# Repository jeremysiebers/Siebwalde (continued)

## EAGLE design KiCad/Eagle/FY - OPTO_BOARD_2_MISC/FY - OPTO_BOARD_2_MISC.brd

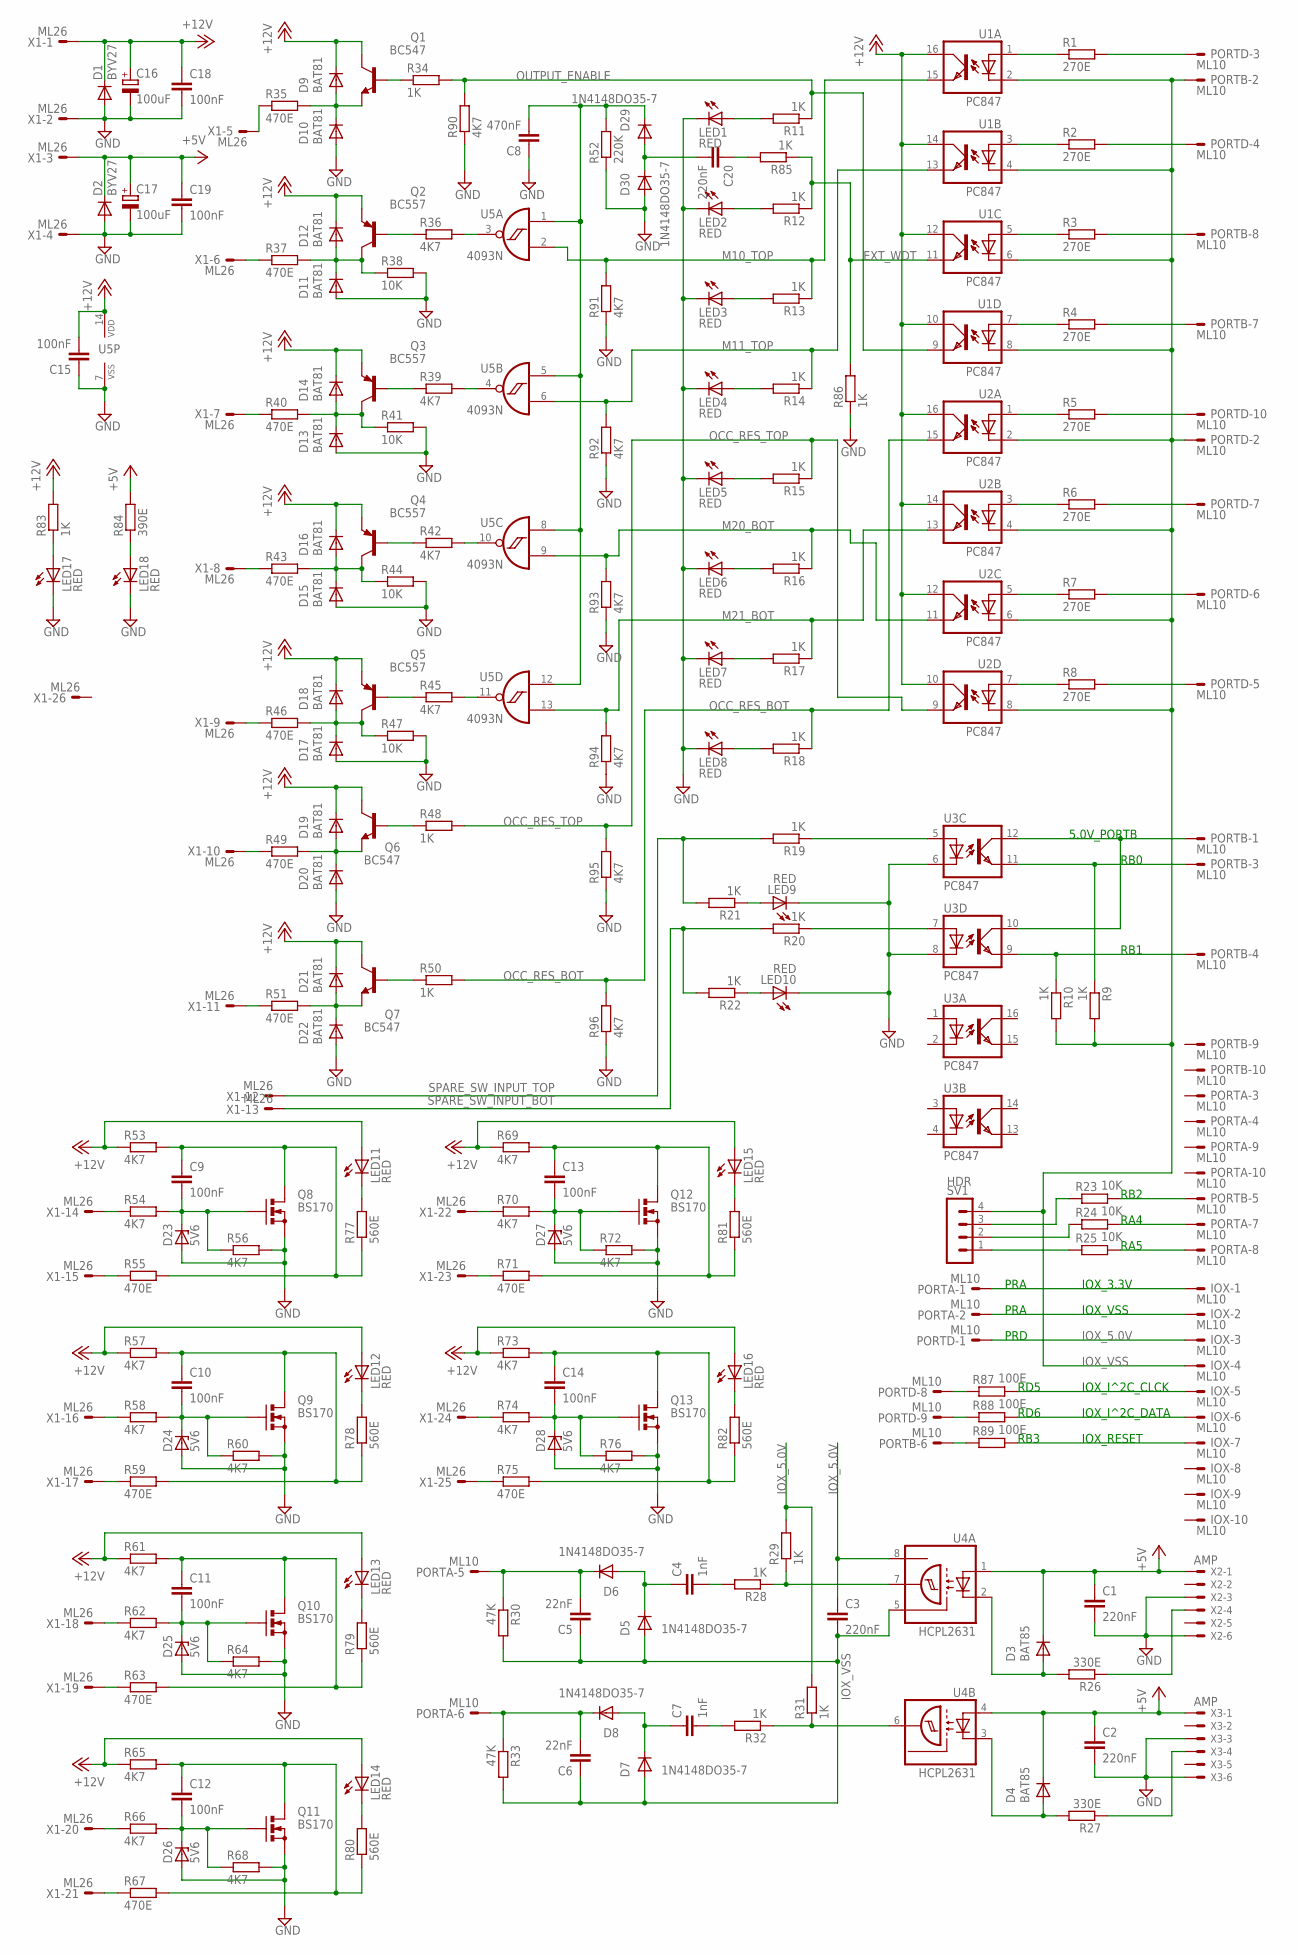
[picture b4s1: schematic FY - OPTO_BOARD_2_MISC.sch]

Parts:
C1, C2, C3, C20: 220nF; C050-025X075
C4, C7: 1nF; C050-025X075
C5, C6: 22nF; C050-025X075
C8: 470nF; C050-025X075
C9, C10, C11, C12, C13, C14, C15, C18, C19: 100nF; C050-025X075
C16, C17: 100uF; E5-8,5
D1, D2: BYV27; SOD57-10
D3, D4: BAT85; DO34-7
D5, D6, D7, D8, D29, D30: 1N4148DO35-7; DO35-7
D9, D10, D11, D12, D13, D14, D15, D16, D17, D18, D19, D20, D21, D22: BAT81; DO34-7
D23, D24, D25, D26, D27, D28: 5V6; DO34Z7
IOX: ML10
LED1, LED2, LED3, LED4, LED5, LED6, LED7, LED8, LED9, LED10, LED11, LED12, LED13, LED14, LED15, LED16, LED17, LED18: RED; LED3MM
PORTA: ML10
PORTB: ML10
PORTD: ML10
Q1, Q6, Q7: BC547; TO92
Q2, Q3, Q4, Q5: BC557; TO92
Q8, Q9, Q10, Q11, Q12, Q13: BS170; SOT54E
R1, R2, R3, R4, R5, R6, R7, R8: 270E; 0207/10
R9, R10, R11, R12, R13, R14, R15, R16, R17, R18, R19, R20, R21, R22, R28, R29, R31, R32, R34, R48, R50, R83, R85, R86: 1K; 0207/10
R23, R24, R25, R38, R41, R44, R47: 10K; 0207/10
R26, R27: 330E; 0207/10
R30, R33: 47K; 0207/10
R35, R37, R40, R43, R46, R49, R51, R55, R59, R63, R67, R71, R75: 470E; 0207/10
R36, R39, R42, R45, R53, R54, R56, R57, R58, R60, R61, R62, R64, R65, R66, R68, R69, R70, R72, R73, R74, R76, R90, R91, R92, R93, R94, R95, R96: 4K7; 0207/10
R52: 220K; 0207/10
R77, R78, R79, R80, R81, R82: 560E; 0207/10
R84: 390E; 0207/10
R87, R88, R89: 100E; 0207/10
SV1: HDR; MA04-1
U1, U2, U3: PC847; DIL16
U4: HCPL2631; DIL08
U5: 4093N; DIL14
X1: ML26
X2, X3: AMP; 22-23-2061

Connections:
+5V: C1.1, C2.1, C17.+, C19.1, D2.C, D3.C, D4.C, R84.2, U4.1 (A), U4.4 (A), X1.3, X2.1, X3.1
+12V: C15.2, C16.+, C18.1, D1.C, D9.C, D12.C, D14.C, D16.C, D18.C, D19.C, D21.C, LED11.A, LED12.A, LED13.A, LED14.A, LED15.A, LED16.A, Q1.3 (C), Q2.1 (E), Q3.1 (E), Q4.1 (E), Q5.1 (E), Q6.3 (C), Q7.3 (C), R53.1, R57.1, R61.1, R65.1, R69.1, R73.1, R83.2, U1.10 (COL), U1.12 (COL), U1.14 (COL), U1.16 (COL), U2.10 (COL), U2.12 (COL), U2.14 (COL), U2.16 (COL), U5.14 (VDD), X1.1
EXT_WDT: R12.1, R85.1, R86.2, U1.11 (EMIT)
GND: C1.2, C2.2, C8.1, C15.1, C16.-, C17.-, C18.2, C19.2, D1.A, D2.A, D10.A, D11.A, D13.A, D15.A, D17.A, D20.A, D22.A, D23.A, D24.A, D25.A, D26.A, D27.A, D28.A, D30.A, LED1.K (C), LED2.K (C), LED3.K (C), LED4.K (C), LED5.K (C), LED6.K (C), LED7.K (C), LED8.K (C), LED9.K (C), LED10.K (C), LED17.K (C), LED18.K (C), Q8.S, Q9.S, Q10.S, Q11.S, Q12.S, Q13.S, R38.2, R41.2, R44.2, R47.2, R52.1, R56.2, R60.2, R64.2, R68.2, R72.2, R76.2, R86.1, R90.1, R91.1, R92.1, R93.1, R94.1, R95.1, R96.1, U3.6 (C), U3.8 (C), U5.7 (VSS), X1.2, X1.4, X2.3, X2.6, X3.3, X3.6
IOX_5.0V: C3.1, IOX.3, PORTD.1, R29.2, R31.2, U4.8 (VCC)
IOX_VSS: C3.2, C5.1, C6.1, D5.A, D7.A, IOX.4, PORTB.2, PORTD.2, R9.2, R10.2, R30.2, R33.2, SV1.4, U1.2 (C), U1.4 (C), U1.6 (C), U1.8 (C), U2.2 (C), U2.4 (C), U2.6 (C), U2.8 (C), U4.5 (GND)
M10_TOP: R13.1, R91.2, U1.15 (EMIT), U5.2 (I1)
M11_TOP: R14.1, R92.2, U1.13 (EMIT), U5.6 (I1)
M20_BOT: R16.1, R93.2, U2.11 (EMIT), U5.9 (I1)
M21_BOT: R17.1, R94.2, U2.13 (EMIT), U5.13 (I1)
unnamed: R1.1, U1.1 (A)
unnamed: R2.1, U1.3 (A)
unnamed: R3.1, U1.5 (A)
unnamed: R4.1, U1.7 (A)
unnamed: LED1.A, R11.2
unnamed: LED2.A, R12.2
unnamed: LED3.A, R13.2
unnamed: LED4.A, R14.2
unnamed: Q2.2 (B), R36.1
unnamed: C10.1, Q9.D, R57.2, R59.2, R78.1
unnamed: C8.2, D29.C, R52.2, U5.1 (I0), U5.5 (I0), U5.8 (I0), U5.12 (I0)
unnamed: LED11.K (C), R77.2
unnamed: R23.1, SV1.3
unnamed: R5.1, U2.1 (A)
unnamed: R6.1, U2.3 (A)
unnamed: R7.1, U2.5 (A)
unnamed: R8.1, U2.7 (A)
unnamed: C9.2, D23.C, Q8.G, R54.2, R56.1
unnamed: R19.1, U3.5 (A)
unnamed: R20.1, U3.7 (A)
unnamed: LED12.K (C), R78.2
unnamed: LED5.A, R15.2
unnamed: LED6.A, R16.2
unnamed: LED7.A, R17.2
unnamed: LED8.A, R18.2
unnamed: PORTD.5, R8.2
unnamed: Q1.2 (B), R34.1
unnamed: PORTD.6, R7.2
unnamed: PORTD.7, R6.2
unnamed: PORTD.10, R5.2
unnamed: PORTD.4, R2.2
unnamed: PORTD.3, R1.2
unnamed: C10.2, D24.C, Q9.G, R58.2, R60.1
unnamed: LED9.A, R21.1
unnamed: LED10.A, R22.1
unnamed: PORTB.1, U3.10 (COL), U3.12 (COL)
unnamed: LED17.A, R83.1
unnamed: PORTB.8, R3.2
unnamed: PORTB.3, R9.1, U3.11 (EMIT)
unnamed: PORTB.4, R10.1, U3.9 (EMIT)
unnamed: PORTB.7, R4.2
unnamed: LED18.A, R84.1
unnamed: C4.2, R28.2
unnamed: R24.1, SV1.2
unnamed: R25.1, SV1.1
unnamed: PORTB.5, R23.2
unnamed: PORTA.7, R24.2
unnamed: PORTA.8, R25.2
unnamed: IOX.1, PORTA.1
unnamed: IOX.2, PORTA.2
unnamed: IOX.7, R89.2
unnamed: IOX.5, R87.2
unnamed: IOX.6, R88.2
unnamed: D9.A, D10.C, Q1.1 (E), R35.2
unnamed: D3.A, R26.2, U4.2 (C)
unnamed: R35.1, X1.5
unnamed: R26.1, X2.4
unnamed: R27.1, X3.4
unnamed: D4.A, R27.2, U4.3 (C)
unnamed: R37.1, X1.6
unnamed: D11.C, D12.A, Q2.3 (C), R37.2, R38.1
unnamed: R36.2, U5.3 (O)
unnamed: R28.1, R29.1, U4.7 (OUT)
unnamed: R31.1, R32.1, U4.6 (OUT)
unnamed: C7.2, R32.2
unnamed: C20.2, D29.A, D30.C
unnamed: C5.2, D6.C, PORTA.5, R30.1
unnamed: C7.1, D7.C, D8.A
unnamed: C4.1, D5.C, D6.A
unnamed: C20.1, R85.2
unnamed: C6.2, D8.C, PORTA.6, R33.1
unnamed: PORTD.8, R87.1
unnamed: Q3.2 (B), R39.1
unnamed: D13.C, D14.A, Q3.3 (C), R40.2, R41.1
unnamed: R40.1, X1.7
unnamed: Q4.2 (B), R42.1
unnamed: D15.C, D16.A, Q4.3 (C), R43.2, R44.1
unnamed: R43.1, X1.8
unnamed: Q5.2 (B), R45.1
unnamed: D17.C, D18.A, Q5.3 (C), R46.2, R47.1
unnamed: R46.1, X1.9
unnamed: R39.2, U5.4 (O)
unnamed: R42.2, U5.10 (O)
unnamed: R45.2, U5.11 (O)
unnamed: D19.A, D20.C, Q6.1 (E), R49.2
unnamed: Q6.2 (B), R48.1
unnamed: R49.1, X1.10
unnamed: D21.A, D22.C, Q7.1 (E), R51.2
unnamed: Q7.2 (B), R50.1
unnamed: R51.1, X1.11
unnamed: C11.2, D25.C, Q10.G, R62.2, R64.1
unnamed: C12.2, D26.C, Q11.G, R66.2, R68.1
unnamed: C13.2, D27.C, Q12.G, R70.2, R72.1
unnamed: C14.2, D28.C, Q13.G, R74.2, R76.1
unnamed: R54.1, X1.14
unnamed: R55.1, X1.15
unnamed: R58.1, X1.16
unnamed: R59.1, X1.17
unnamed: R62.1, X1.18
unnamed: R63.1, X1.19
unnamed: R66.1, X1.20
unnamed: R67.1, X1.21
unnamed: R70.1, X1.22
unnamed: R71.1, X1.23
unnamed: R74.1, X1.24
unnamed: R75.1, X1.25
unnamed: LED13.K (C), R79.2
unnamed: LED14.K (C), R80.2
unnamed: LED15.K (C), R81.2
unnamed: LED16.K (C), R82.2
unnamed: PORTD.9, R88.1
unnamed: PORTB.6, R89.1
unnamed: C9.1, Q8.D, R53.2, R55.2, R77.1
unnamed: C11.1, Q10.D, R61.2, R63.2, R79.1
unnamed: C12.1, Q11.D, R65.2, R67.2, R80.1
unnamed: C14.1, Q13.D, R73.2, R75.2, R82.1
unnamed: C13.1, Q12.D, R69.2, R71.2, R81.1
OCC_RES_BOT: R18.1, R50.2, R96.2, U2.15 (EMIT)
OCC_RES_TOP: R15.1, R48.2, R95.2, U2.9 (EMIT)
OUTPUT_ENABLE: R11.1, R34.2, R90.2, U1.9 (EMIT)
SPARE_SW_INPUT_BOT: R20.2, R22.2, X1.13
SPARE_SW_INPUT_TOP: R19.2, R21.2, X1.12

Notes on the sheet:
IOX_RESET
IOX_I^2C_DATA
IOX_I^2C_CLCK
IOX_VSS
IOX_3.3V
5.0V_PORTB
RB0
RB1
RB2
RA4
RA5
PRA
PRD
RD5
RD6
RB3

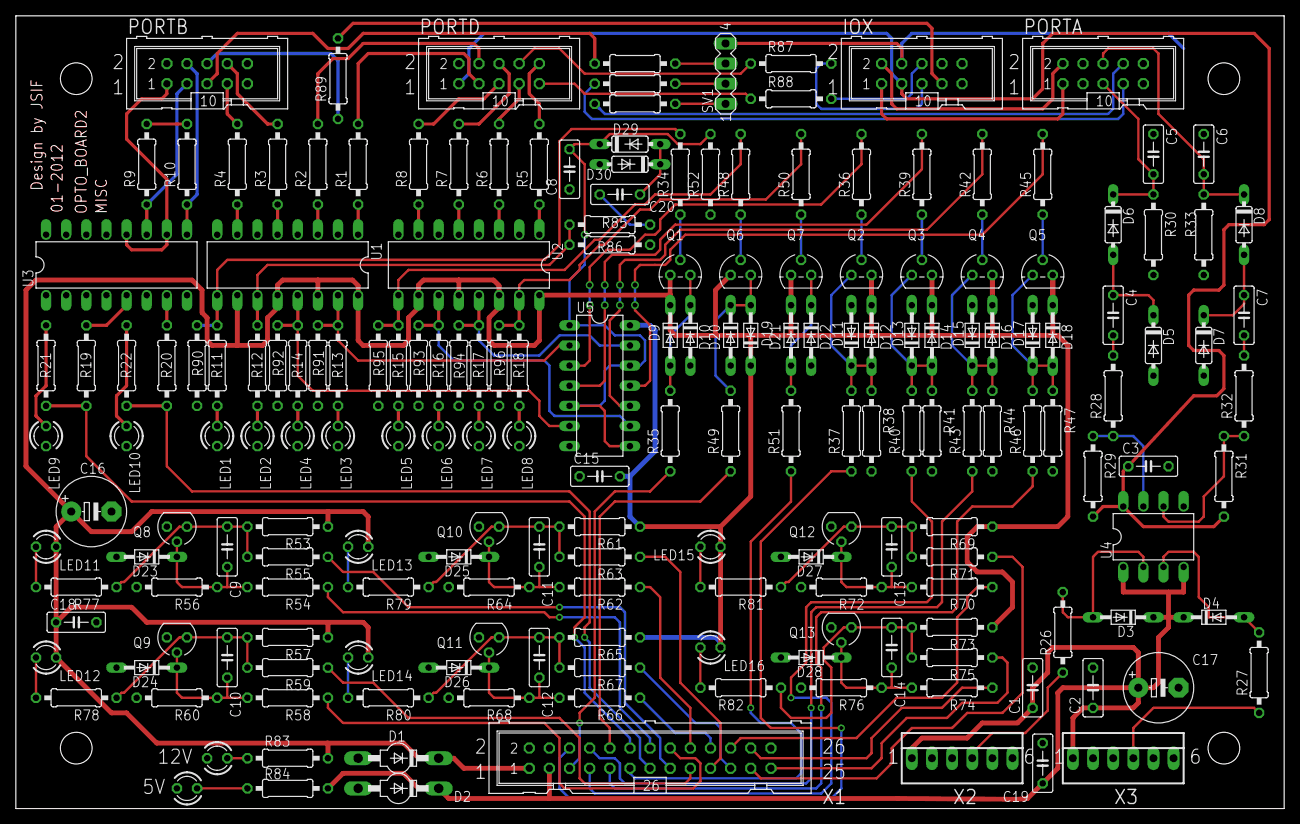
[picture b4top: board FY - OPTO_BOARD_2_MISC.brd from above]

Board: 2 copper layers, 160.0 x 100.0 mm, 190 parts (0 on the bottom side), 132 nets.

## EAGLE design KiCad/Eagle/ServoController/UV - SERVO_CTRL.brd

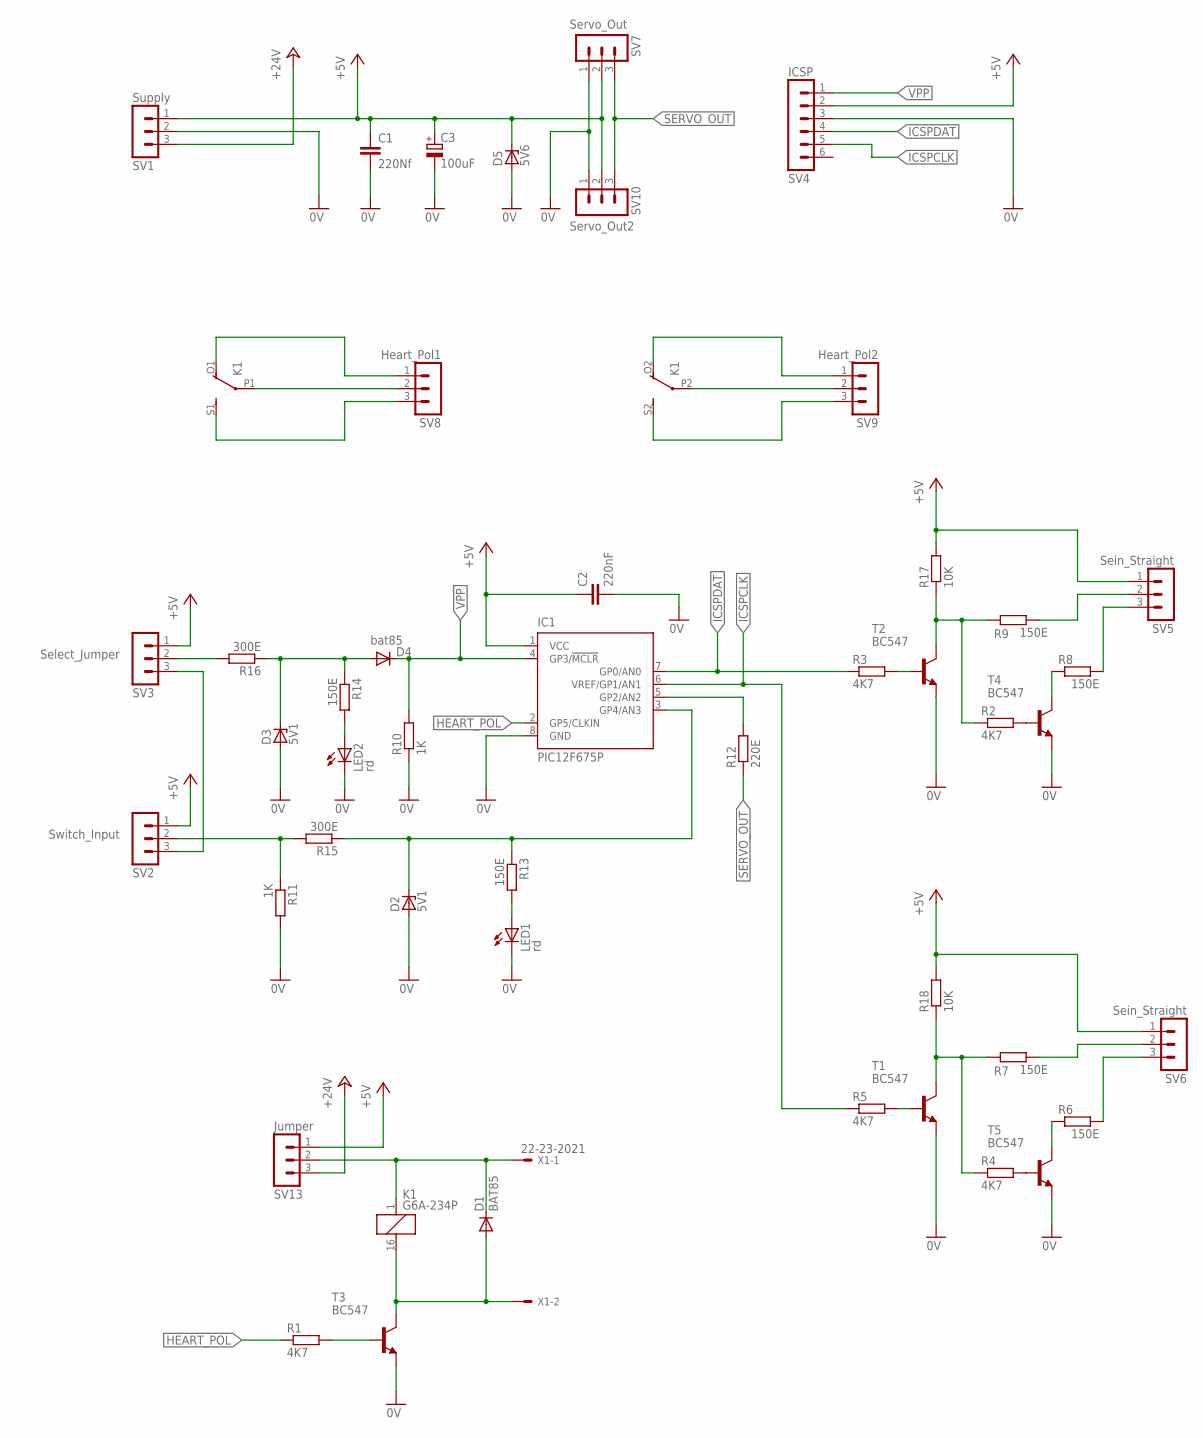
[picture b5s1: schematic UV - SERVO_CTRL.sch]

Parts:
C1: 220Nf; C050-025X075; MPN MCPBSFC-1J222KA45
C2: 220nF; C050-025X075; MPN MCPBSFC-1J222KA45
C3: 100uF; E2,5-7; MPN 107CKE035M
D1: BAT85; DO34-7; MPN BAT85,113
D2, D3: 5V1; DO34Z7; MPN BZX55C5V1-TAP
D4: bat85; DO34-7; MPN BAT85,113
D5: 5V6; C1702-15; MPN BZX85C5V1
IC1: PIC12F675P; DIL8; MPN PIC12F675-E/P
K1: G6A-234P; MPN G6A-234P-ST40-US-DC12
LED1, LED2: rd; LED3MM; MPN L-934ND
R1, R2, R3, R4, R5: 4K7; 0207/2V; MPN MCF 0.25W 4K7
R6, R7, R8, R9, R13, R14: 150E; 0207/2V; MPN MCF 0.25W 150R
R10, R11: 1K; 0207/2V; MPN MCF 0.25W 1K
R12: 220E; 0207/2V; MPN MCF 0.25W 220R
R15, R16: 300E; 0207/2V; MPN MF25 300R
R17, R18: 10K; 0207/2V; MPN MCF 0.25W 10K
SV1: Supply; MA03-1; MPN 90120-0761
SV2: Switch_Input; MA03-1; MPN 90120-0761
SV3: Select_Jumper; MA03-1; MPN 90120-0761
SV4: ICSP; MA06-1; MPN 90120-0761
SV5, SV6: Sein_Straight; MA03-1; MPN 90120-0761
SV7: Servo_Out; MA03-1; MPN 90120-0761
SV8: Heart_Pol1; MA03-1; MPN 90120-0761
SV9: Heart_Pol2; MA03-1; MPN 90120-0761
SV10: Servo_Out2; MA03-1; MPN 90120-0761
SV13: Jumper; MA03-1; MPN 90120-0761
T1, T2, T3, T4, T5: BC547; TO92; MPN BC547B
X1: 22-23-2021; MPN 22-23-2021

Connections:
0V: C1.2, C2.2, C3.-, D2.A, D3.A, D5.A, IC1.8 (GND), LED1.K (C), LED2.K (C), R10.1, R11.2, SV1.2, SV4.3, SV7.1, SV10.1, T1.1 (E), T2.1 (E), T3.1 (E), T4.1 (E), T5.1 (E)
+5V: C1.1, C2.1, C3.+, D5.C, IC1.1 (VCC), R17.2, R18.2, SV1.1, SV2.1, SV3.1, SV4.2, SV5.1, SV6.1, SV7.2, SV10.2, SV13.1
+24V: SV1.3, SV13.3
HEART_POL: IC1.2 (GP5/CLKIN), R1.1
ICSPCLK: IC1.6 (VREF/GP1/AN1), R5.1, SV4.5
ICSPDAT: IC1.7 (GP0/AN0), R3.1, SV4.4
unnamed: D2.C, IC1.3 (GP4/AN3), R13.1, R15.1
unnamed: K1.O1 (O), SV8.1
unnamed: SV2.3, SV3.3
unnamed: K1.S1 (S), SV8.3
unnamed: K1.P1, SV8.2
unnamed: K1.O2 (O), SV9.1
unnamed: K1.S2 (S), SV9.3
unnamed: K1.P2, SV9.2
unnamed: IC1.5 (GP2/AN2), R12.2
unnamed: R1.2, T3.2 (B)
unnamed: D1.C, K1.1, SV13.2, X1.1
unnamed: D1.A, K1.16 (2), T3.3 (C), X1.2
unnamed: R4.2, T5.2 (B)
unnamed: R6.1, T5.3 (C)
unnamed: R6.2, SV6.3
unnamed: R5.2, T1.2 (B)
unnamed: R11.1, R15.2, SV2.2
unnamed: R4.1, R7.1, R18.1, T1.3 (C)
unnamed: R7.2, SV6.2
unnamed: R2.2, T4.2 (B)
unnamed: R8.1, T4.3 (C)
unnamed: R8.2, SV5.3
unnamed: R9.2, SV5.2
unnamed: R2.1, R9.1, R17.1, T2.3 (C)
unnamed: R3.2, T2.2 (B)
unnamed: D3.C, D4.A, R14.1, R16.1
unnamed: LED2.A, R14.2
unnamed: LED1.A, R13.2
unnamed: R16.2, SV3.2
SERVO_OUT: R12.1, SV7.3, SV10.3
VPP: D4.C, IC1.4 (GP3/!MCLR), R10.2, SV4.1

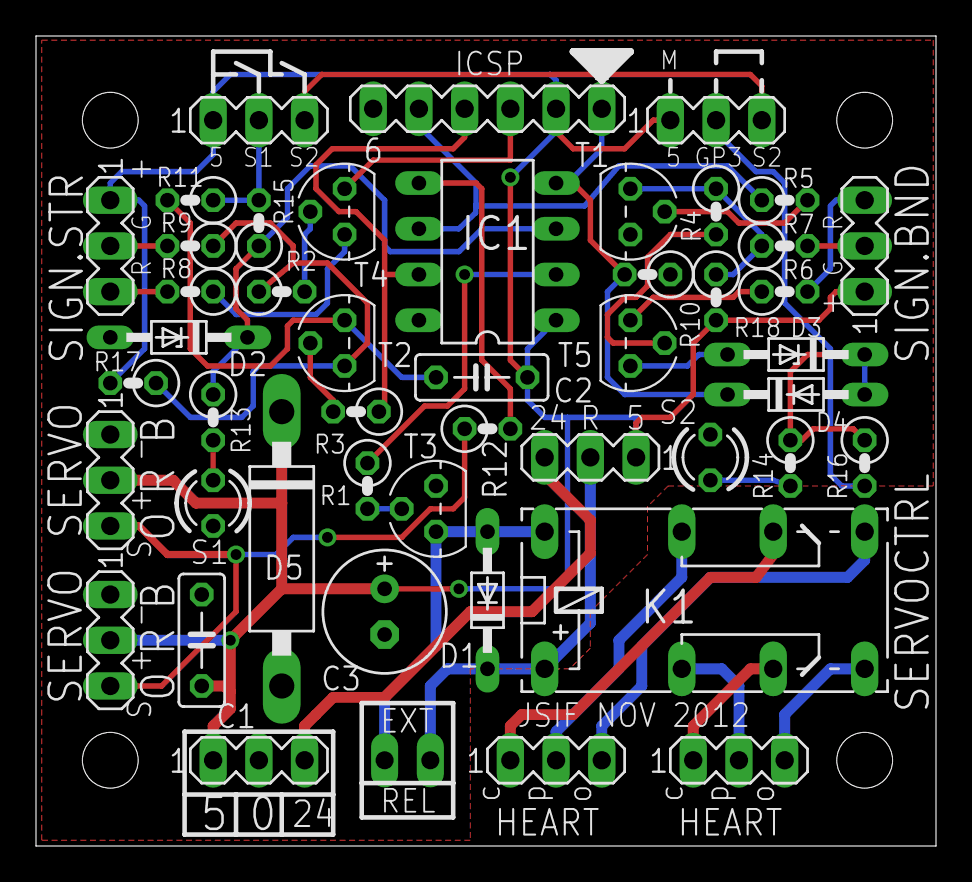
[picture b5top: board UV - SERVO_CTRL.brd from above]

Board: 2 copper layers, 50.0 x 45.0 mm, 47 parts (0 on the bottom side), 37 nets.

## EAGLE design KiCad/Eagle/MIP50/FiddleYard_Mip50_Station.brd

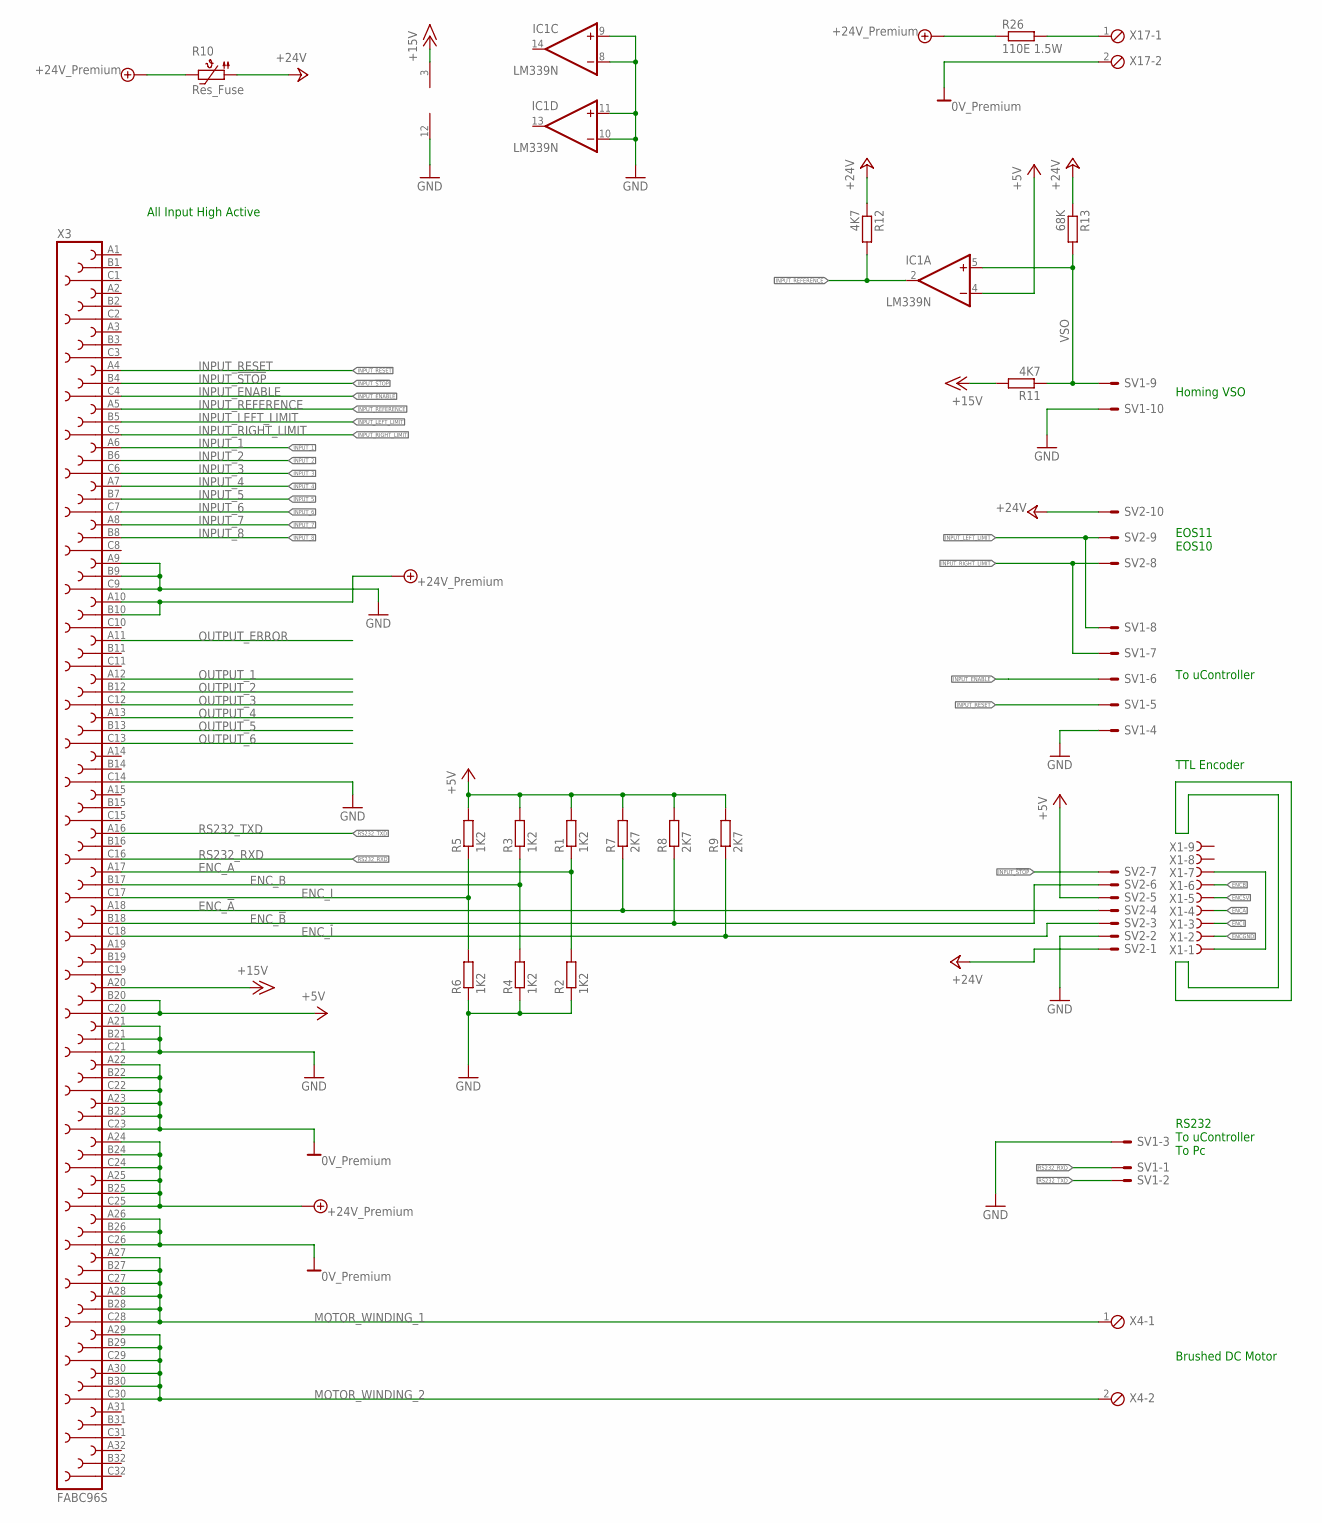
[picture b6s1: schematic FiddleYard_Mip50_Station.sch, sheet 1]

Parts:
IC1: LM339N; DIL14
R1, R2, R3, R4, R5, R6: 1K2; 0204V
R7, R8, R9: 2K7; 0204V
R10: Res_Fuse; SOD70
R11, R12: 4K7; 0204V
R13: 68K; 0204V
R26: 110E 1.5W; 0204V
SV1, SV2: ML10E; ML10
X1: F09VS; F09V
X3: FABC96S
X4, X17: MPT2; 2POL254

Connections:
0V: X3.A22, X3.A23, X3.A26, X3.B22, X3.B23, X3.B26, X3.C22, X3.C23, X3.C26, X17.2; also elsewhere on the board
+5V: IC1.4 (-IN), R1.2, R3.2, R5.2, R7.2, R8.2, R9.2, SV2.5; also elsewhere on the board
+15V: IC1.3 (V+), R11.2, X3.A20; also elsewhere on the board
+24V: R10.1, R10.2, R12.1, R13.1, R26.1, SV2.1, SV2.10, X3.A10, X3.A24, X3.A25, X3.B10, X3.B24, X3.B25, X3.C24, X3.C25; also elsewhere on the board
ENC5V: X1.5; also elsewhere on the board
ENCA: X1.4; also elsewhere on the board
ENCB: X1.6; also elsewhere on the board
ENCGND: X1.2; also elsewhere on the board
ENCI: X1.3; also elsewhere on the board
ENC_!A: R7.1, SV2.4, X3.A18; also elsewhere on the board
ENC_!B: R8.1, SV2.6, X3.B18; also elsewhere on the board
ENC_!I: R9.1, SV2.3, X3.C18; also elsewhere on the board
ENC_+5V: X3.B20, X3.C20; also elsewhere on the board
ENC_A: R1.1, R2.2, X3.A17; also elsewhere on the board
ENC_B: R3.1, R4.2, X3.B17; also elsewhere on the board
ENC_I: R5.1, R6.2, X3.C17; also elsewhere on the board
GND: IC1.8 (-IN), IC1.9 (+IN), IC1.10 (-IN), IC1.11 (+IN), IC1.12 (GND), R2.1, R4.1, R6.1, SV1.3, SV1.4, SV1.10, SV2.2, X3.A9, X3.A21, X3.B9, X3.B21, X3.C9, X3.C14, X3.C21; also elsewhere on the board
INPUT_1: X3.A6; also elsewhere on the board
INPUT_2: X3.B6; also elsewhere on the board
INPUT_3: X3.C6; also elsewhere on the board
INPUT_4: X3.A7; also elsewhere on the board
INPUT_5: X3.B7; also elsewhere on the board
INPUT_6: X3.C7; also elsewhere on the board
INPUT_7: X3.A8; also elsewhere on the board
INPUT_8: X3.B8; also elsewhere on the board
INPUT_!STOP: SV2.7, X3.B4; also elsewhere on the board
INPUT_ENABLE: SV1.6, X3.C4; also elsewhere on the board
INPUT_LEFT_LIMIT: SV1.8, SV2.9, X3.B5; also elsewhere on the board
INPUT_REFERENCE: IC1.2 (OUT), R12.2, X3.A5; also elsewhere on the board
INPUT_RESET: SV1.5, X3.A4; also elsewhere on the board
INPUT_RIGHT_LIMIT: SV1.7, SV2.8, X3.C5; also elsewhere on the board
MOTOR_WINDING_1: X3.A27, X3.A28, X3.B27, X3.B28, X3.C27, X3.C28, X4.1; also elsewhere on the board
MOTOR_WINDING_2: X3.A29, X3.A30, X3.B29, X3.B30, X3.C29, X3.C30, X4.2; also elsewhere on the board
unnamed: X1.1, X1.7
unnamed: R26.2, X17.1
OUTPUT_1: X3.A12; also elsewhere on the board
OUTPUT_2: X3.B12; also elsewhere on the board
OUTPUT_3: X3.C12; also elsewhere on the board
OUTPUT_4: X3.A13; also elsewhere on the board
OUTPUT_5: X3.B13; also elsewhere on the board
OUTPUT_6: X3.C13; also elsewhere on the board
OUTPUT_ERROR: X3.A11; also elsewhere on the board
RS232_RXD: SV1.1, X3.C16; also elsewhere on the board
RS232_TXD: SV1.2, X3.A16; also elsewhere on the board
VSO: IC1.5 (+IN), R11.1, R13.2, SV1.9; also elsewhere on the board

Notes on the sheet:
All Input High Active
To uController
EOS11 EOS10
Homing VSO
TTL Encoder
RS232 To uController To Pc
Brushed DC Motor

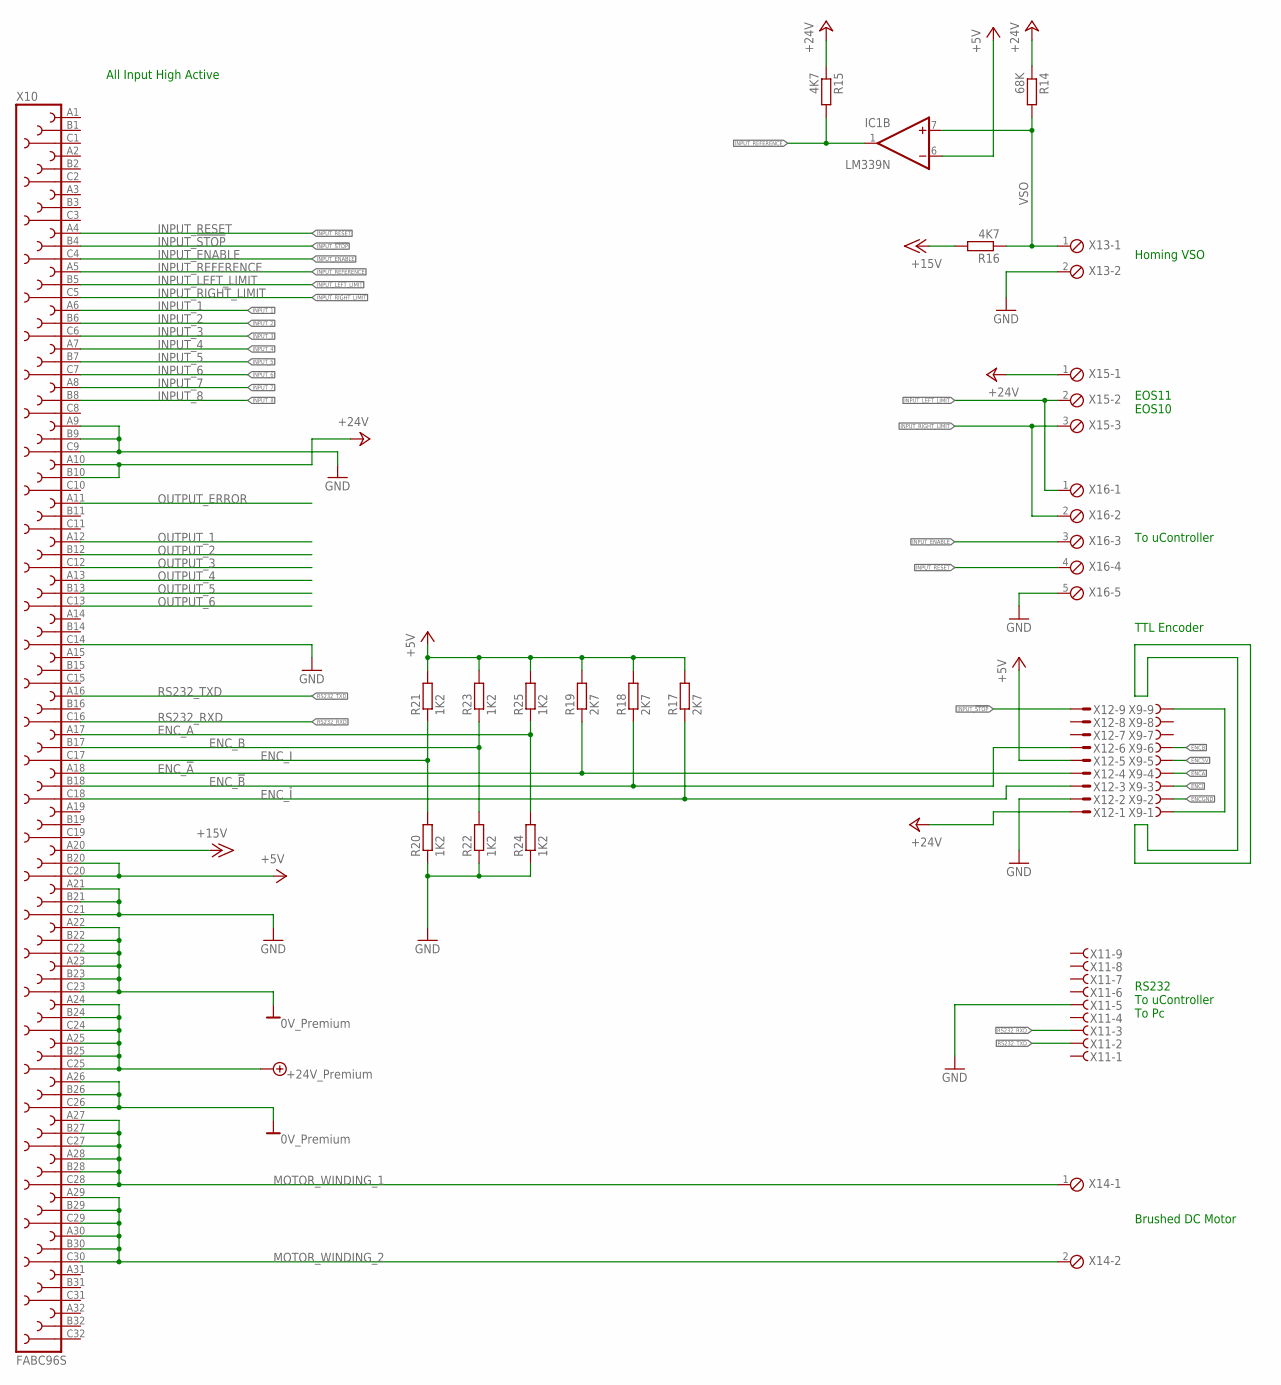
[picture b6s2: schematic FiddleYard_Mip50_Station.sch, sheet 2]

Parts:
IC1: LM339N; DIL14
R14: 68K; 0204V
R15, R16: 4K7; 0204V
R17, R18, R19: 2K7; 0204V
R20, R21, R22, R23, R24, R25: 1K2; 0204V
X9, X11: F09VS; F09V
X10: FABC96S
X12: M09VBS; M09VB
X13, X14: MPT2; 2POL254
X15: MPT3; 3POL254
X16: MPT5; 5POL254

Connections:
0V: X10.A22, X10.A23, X10.A26, X10.B22, X10.B23, X10.B26, X10.C22, X10.C23, X10.C26; also elsewhere on the board
+5V: R17.2, R18.2, R19.2, R21.2, R23.2, R25.2, X12.5; also elsewhere on the board
+15V: R16.2, X10.A20; also elsewhere on the board
+24V: R14.1, R15.1, X10.A10, X10.A24, X10.A25, X10.B10, X10.B24, X10.B25, X10.C24, X10.C25, X12.1, X15.1; also elsewhere on the board
ENC5V: X9.5; also elsewhere on the board
ENCA: X9.4; also elsewhere on the board
ENCB: X9.6; also elsewhere on the board
ENCGND: X9.2; also elsewhere on the board
ENCI: X9.3; also elsewhere on the board
ENC_!A: R19.1, X10.A18, X12.4; also elsewhere on the board
ENC_!B: R18.1, X10.B18, X12.6; also elsewhere on the board
ENC_!I: R17.1, X10.C18, X12.3; also elsewhere on the board
ENC_+5V: X10.B20, X10.C20; also elsewhere on the board
ENC_A: R24.2, R25.1, X10.A17; also elsewhere on the board
ENC_B: R22.2, R23.1, X10.B17; also elsewhere on the board
ENC_I: R20.2, R21.1, X10.C17; also elsewhere on the board
GND: R20.1, R22.1, R24.1, X10.A9, X10.A21, X10.B9, X10.B21, X10.C9, X10.C14, X10.C21, X11.5, X12.2, X13.2, X16.5; also elsewhere on the board
INPUT_1: X10.A6; also elsewhere on the board
INPUT_2: X10.B6; also elsewhere on the board
INPUT_3: X10.C6; also elsewhere on the board
INPUT_4: X10.A7; also elsewhere on the board
INPUT_5: X10.B7; also elsewhere on the board
INPUT_6: X10.C7; also elsewhere on the board
INPUT_7: X10.A8; also elsewhere on the board
INPUT_8: X10.B8; also elsewhere on the board
INPUT_!STOP: X10.B4, X12.9; also elsewhere on the board
INPUT_ENABLE: X10.C4, X16.3; also elsewhere on the board
INPUT_LEFT_LIMIT: X10.B5, X15.2, X16.1; also elsewhere on the board
INPUT_REFERENCE: R15.2, X10.A5; also elsewhere on the board
INPUT_RESET: X10.A4, X16.4; also elsewhere on the board
INPUT_RIGHT_LIMIT: X10.C5, X15.3, X16.2; also elsewhere on the board
MOTOR_WINDING_1: X10.A27, X10.A28, X10.B27, X10.B28, X10.C27, X10.C28, X14.1; also elsewhere on the board
MOTOR_WINDING_2: X10.A29, X10.A30, X10.B29, X10.B30, X10.C29, X10.C30, X14.2; also elsewhere on the board
unnamed: X9.1, X9.9
OUTPUT_1: X10.A12; also elsewhere on the board
OUTPUT_2: X10.B12; also elsewhere on the board
OUTPUT_3: X10.C12; also elsewhere on the board
OUTPUT_4: X10.A13; also elsewhere on the board
OUTPUT_5: X10.B13; also elsewhere on the board
OUTPUT_6: X10.C13; also elsewhere on the board
OUTPUT_ERROR: X10.A11; also elsewhere on the board
RS232_RXD: X10.C16, X11.3; also elsewhere on the board
RS232_TXD: X10.A16, X11.2; also elsewhere on the board
VSO: R14.2, R16.1, X13.1; also elsewhere on the board

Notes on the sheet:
All Input High Active
To uController
EOS11 EOS10
Homing VSO
TTL Encoder
RS232 To uController To Pc
Brushed DC Motor

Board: 2 copper layers, 41 parts (0 on the bottom side), 46 nets, no tracks yet.
